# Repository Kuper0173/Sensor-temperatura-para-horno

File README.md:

# Sensor Inteligente 🌐🔧

¡Bienvenido al repositorio del Proyecto Sensor Inteligente!

## Descripción del Proyecto
El Sensor Inteligente es un proyecto diseñado para [breve descripción del proyecto]. Este repositorio contiene la información esencial para entender, implementar y mejorar el proyecto.

## Contenido del Repositorio  📂

### 1. Software 🖥️
La carpeta `software` contiene el código fuente y cualquier recurso relacionado con el software necesario para el funcionamiento del Sensor Inteligente.

### 2. Hardware 🛠️
La carpeta `hardware` almacena toda la información relacionada con el diseño y la configuración del hardware, incluyendo esquemáticos, archivos de diseño de PCB, y cualquier otra documentación relevante.

### 3. Diagramas 📊
La carpeta `diagramas` incluye diagramas visuales, como diagramas de flujo, diagramas de conexiones y otros gráficos que ayudan a comprender la arquitectura y el funcionamiento del Sensor Inteligente.

### 4. Diseño del case :📱
La carpeta diseño del case contiene los archivos que se usaron para la creación del case del proyecto.

### 5. Ingenia futuro 🎉
En esta carpeta se encuentran los archivos pertenecientes al evento de ingenina futuro realizado en la Universidad Nacional de Colombia.

### 6. PCB 📏
La carpeta de PCB contiene los archivos y la explicación de la creación de la placa PCB para que pueda ser impresa cuando se necesite.

### Wiki 📖
La sección de [Wiki](../../wiki) del repositorio contiene la documentación completa del proyecto. Aquí encontrarás explicaciones, guías de instalación, detalles técnicos y cualquier otra información relevante.

## Cómo Contribuir 🤝
¡Agradecemos tus contribuciones al proyecto! Si deseas contribuir, sigue estos pasos:

1. **Fork:** Haz un fork de este repositorio.
2. **Crea una Rama:** Crea una rama para tu contribución.
3. **Realiza Cambios:** Realiza tus modificaciones.
4. **Envía un Pull Request:** Envía un pull request desde tu rama a la rama principal de este repositorio.

## Problemas y Mejoras
Si encuentras problemas o tienes ideas para mejorar el proyecto, por favor, abre un issue en la sección de [Issues](../../issues) del repositorio.

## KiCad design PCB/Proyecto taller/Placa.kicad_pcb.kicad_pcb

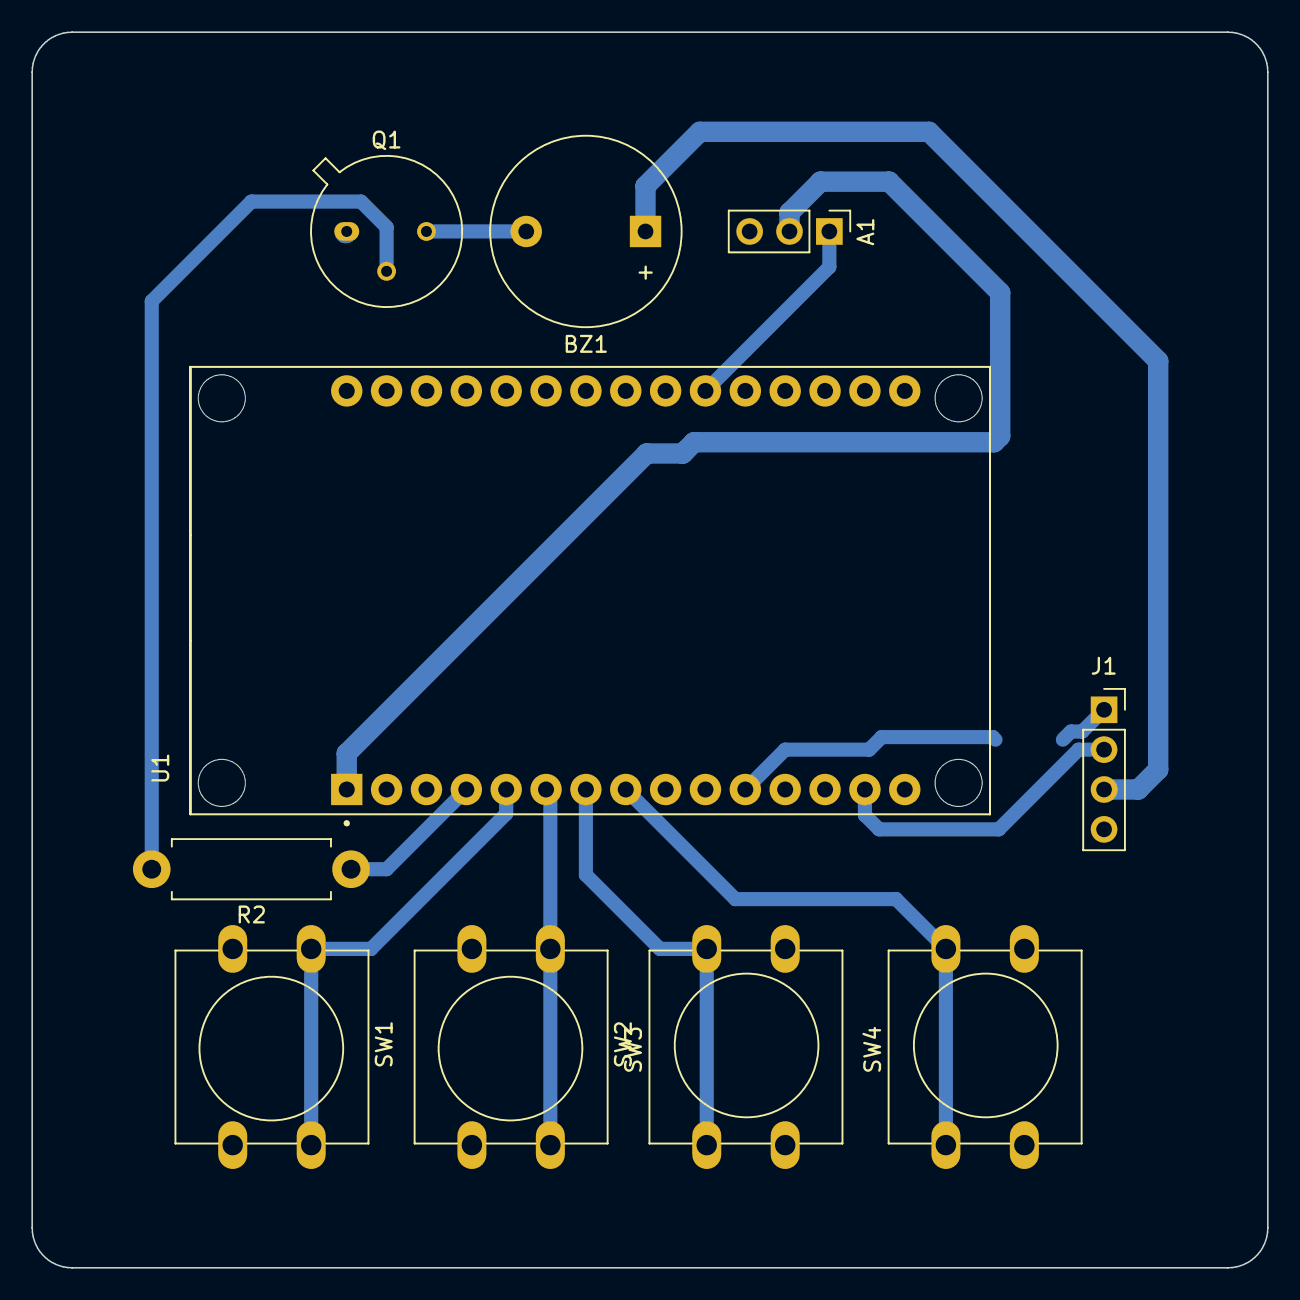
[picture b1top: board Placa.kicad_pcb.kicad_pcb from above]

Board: 2 copper layers, 78.7 x 78.7 mm, 10 parts (0 on the bottom side), 13 nets.

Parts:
A1: LM35DZ_NOPB; PinHeader_1x03_P2.54mm_Vertical
BZ1: Buzzer; Buzzer_12x9.5RM7.6
J1: Conn_01x04_Socket; PinSocket_1x04_P2.54mm_Vertical
Q1: 2N2219; TO-39-3
R2: 4700; R_Axial_DIN0411_L9.9mm_D3.6mm_P12.70mm_Horizontal
SW1, SW2, SW3, SW4: SW_Push_Dual; SW_PUSH-12mm
U1: ESP32-DEVKIT-V1; MODULE_ESP32_DEVKIT_V1

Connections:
+3.3V: A1.2 (VOUT), U1.1 (3V3)
+5V: BZ1.1 (-), J1.3, U1.30 (VIN)
/D2: R2.1, U1.4 (D2)
/D4: SW1.1, U1.5 (D4)
/D5: SW4.1, U1.8 (D5)
/D16: SW2.1, U1.6 (RX2)
/D17: SW3.1, U1.7 (TX2)
/D21: J1.1, U1.11 (D21)
/D22: J1.2, U1.14 (D22)
/D32: A1.1 (+VS), U1.21 (D32)
GND: A1.3 (GND), J1.4, Q1.1 (E), SW1.2, SW2.2, SW3.2, SW4.2, U1.2 (GND), U1.29 (GND)
unnamed: BZ1.2 (+), Q1.3 (C)
unnamed: Q1.2 (B), R2.2

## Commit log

2023-11-30 Create Componentes
